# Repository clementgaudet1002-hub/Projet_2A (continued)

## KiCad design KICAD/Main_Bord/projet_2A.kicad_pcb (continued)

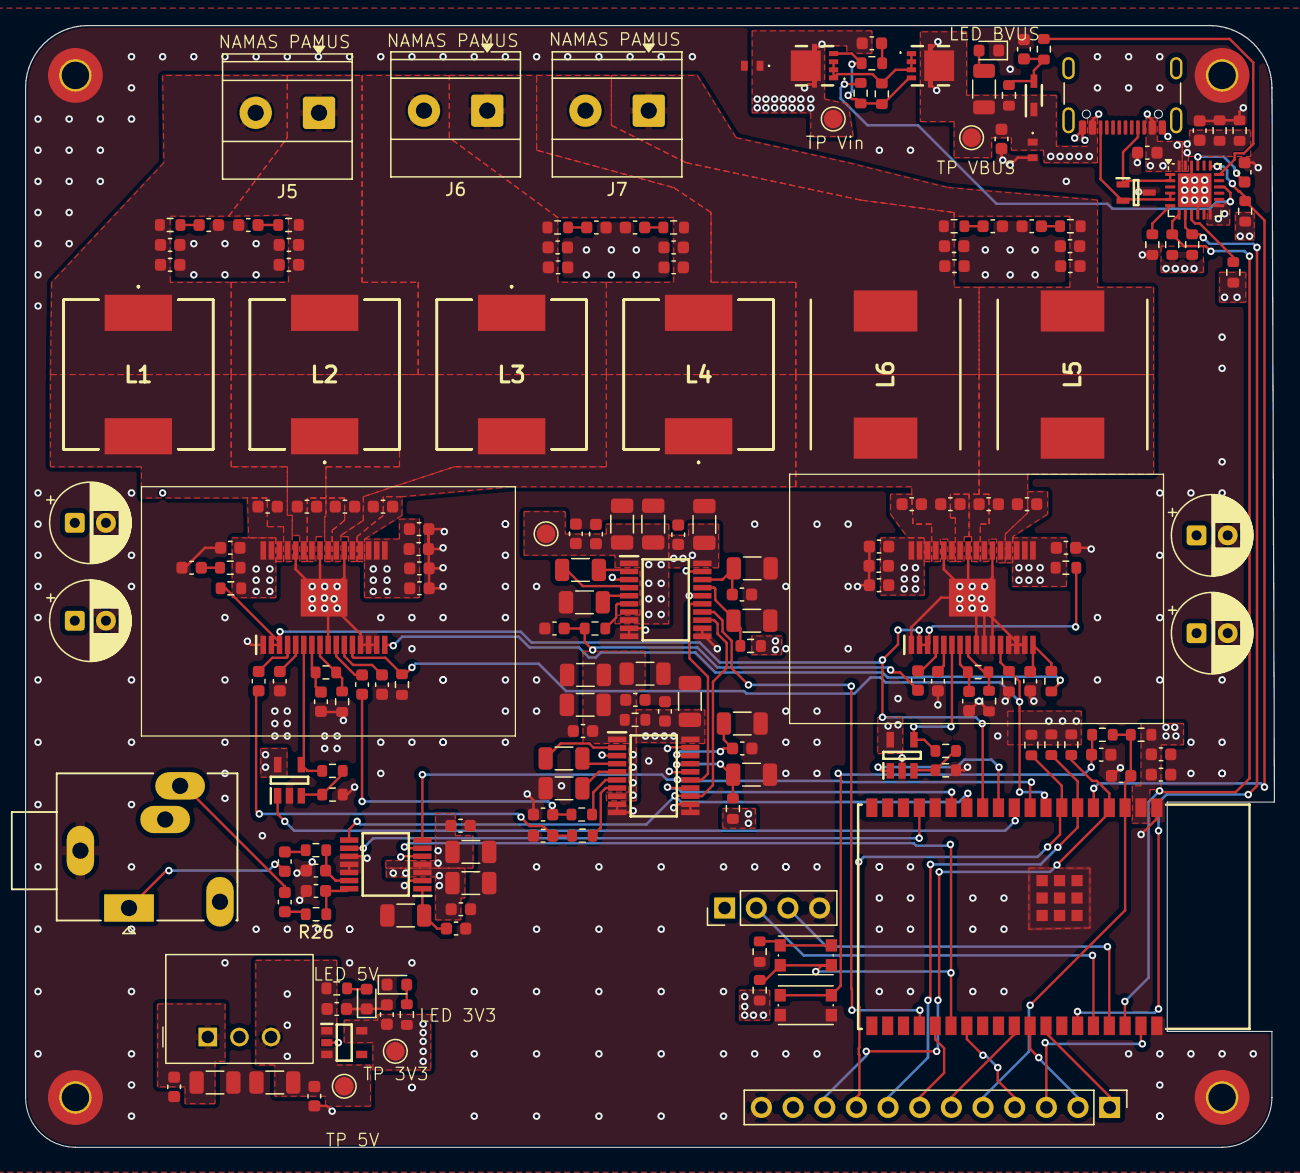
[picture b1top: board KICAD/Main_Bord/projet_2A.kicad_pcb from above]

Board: 4 copper layers, 100.2 x 90.0 mm, 195 parts (0 on the bottom side), 114 nets.

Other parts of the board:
L5, L6: 7447707100

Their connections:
unnamed 79: L5.1; also elsewhere on the board
unnamed 80: L6.2; also elsewhere on the board
unnamed 105: L5.2; also elsewhere on the board
unnamed 106: L6.1; also elsewhere on the board

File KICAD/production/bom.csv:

Designator,Footprint,Quantity,Value,LCSC Part #
"C1, C109, C16, C4, C51, C52, C54, C55, C57, C60, C64, C71, C73, C75, C78, C83, C85, C87, C89, C94, C95",0603,21,100n,
"C10, C15, C20, C22, C24, C25, C3, C39, C40, C41, C43, C44, C45, C6, C7, C9, C96",0603,17,1n,
"C100, C101, C102, C103, C108, C37, C38, C42, C8, C90, C93, C98, C99",0603,13,1u,
"C104, C105, C2, C26, C27, C28, C29, C91, C92",0603,9,10n,
C106,0603,1,4.7u,
C107,0603,1,22u,
"C11, C12, C13, C14, C46, C47, C48, C50",0603,8,220n,
"C110, C66, C67",0603,3,2.2n,
"C17, C5, C53, C56",CP_Radial_D6.3mm_P2.50mm,4,220u,
"C18, C19, C21, C23",0603,4,680n,
"C58, C59, C61, C65, C68, C69, C70, C76, C77, C82, C84, C86, C88, C97",1206,14,10u,
"C62, C63, C72, C74, C80, C81",1206,6,2.2u,
"D1, D3",ESDA25P351U1M,2,ESDA25P35-1U1M,
"D2, D6, D7",0603,3,LED,
D4,ESDA25W,1,ESDA25W,
D5,BAT54JFILM,1,BAT54JFILM,
"IC1, IC2",TPA3116D2QDADRQ1,2,TPA3116D2QDADRQ1,
"IC3, IC4",LM321SN3T1G,2,LM321SN3T1G,
IC5,ESP32WROVEREN16R8,1,ESP32-WROVER-E-N16R8,
"IC6, IC8",PCM5102AQPWRQ1,2,PCM5102AQPWRQ1,
IC7,PCM1808PW,1,PCM1808PW,
"J1, J9",PinHeader_1x12_P2.54mm_Vertical,2,Conn_01x12,
J10,PinHeader_1x04_P2.54mm_Vertical,1,Conn_01x04,
J2,USB_C_Receptacle_GCT_USB4105-xx-A_16P_TopMnt_Horizontal,1,USB_C_Receptacle_USB2.0_16P,
J3,PinHeader_1x09_P2.54mm_Vertical,1,Conn_01x09,
"J5, J6, J7","TerminalBlock_Phoenix_MKDS-1,5-2-5.08_1x02_P5.08mm_Horizontal",3,Conn_01x02,
J8,Jack_3.5mm_Ledino_KB3SPRS_Horizontal,1,AudioJack3_SwitchTR,
"L1, L2, L3, L4",7447706100,4,7447706100,
"L5, L6",7447707100,2,7447707100,
PS2,BU33SD5WG-TR,1,BU33SD5WG-TR,
"Q3, Q4",STL8N10F7,2,STL6P3LLH6,
"R1, R14, R15, R3, R33, R36, R37, R5",0603,8,100k,
R11,0603,1,47k,
R12,0603,1,75k,
"R13, R16, R2, R6, R7, R8, R9",0603,7,3.3,
"R18, R19, R22, R31, R52",0603,5,470,
R20,0603,1,2.2,
"R21, R23, R24, R25, R44, R45, R46, R51",0603,8,10k,
"R26, R27, R35",0603,3,100,
"R28, R42",0603,2,12k,
"R29, R30, R38, R39, R40",0603,5,1k,
"R32, R43",0603,2,13k,
R34,0603,1,22k,
R4,0603,1,20k,
R41,1206,1,4.7k,
"R47, R48, R49",0603,3,4.7k,
R50,0603,1,0,
SW1,RotaryEncoder_Alps_EC11E-Switch_Vertical_H20mm_CircularMountingHoles,1,RotaryEncoder_Switch,
SW2,SW_PUSH_6mm,1,SW_Push,
"SW3, SW4",SW_Push_1P1T_NO_CK_KMR2,2,SW_Push,
"TP2, TP4, TP6, TP7, TP8",TestPoint_Pad_D1.5mm,5,TestPoint,
U3,QFN-24-1EP_4x4mm_P0.5mm_EP2.7x2.7mm,1,STUSB4500QTR,
U6,U_Wurth_MagIC-FDSM_173010x42,1,173010542,

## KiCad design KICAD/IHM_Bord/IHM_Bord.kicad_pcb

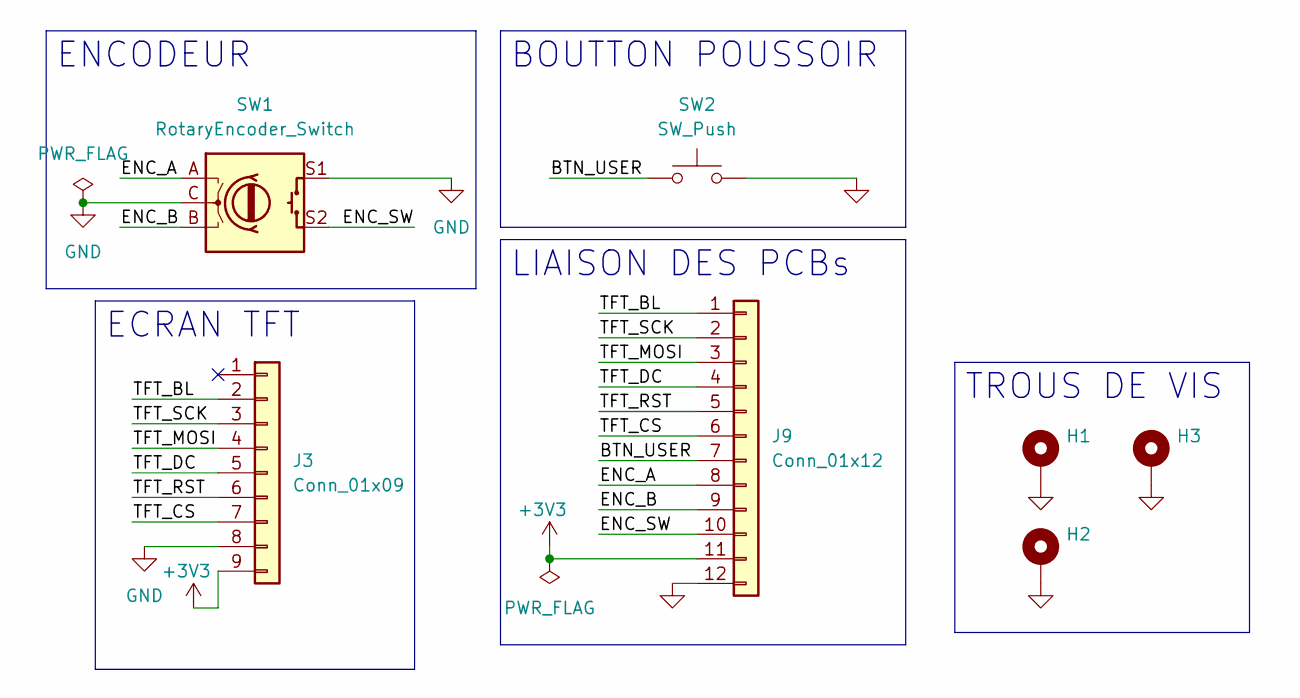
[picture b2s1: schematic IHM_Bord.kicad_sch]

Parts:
H1, H2, H3: MountingHole_Pad; MountingHole_2.2mm_M2_Pad_TopBottom
J3: Conn_01x09; PinHeader_1x09_P2.54mm_Vertical
J9: Conn_01x12; PinHeader_1x12_P2.54mm_Vertical
SW1: RotaryEncoder_Switch; RotaryEncoder_Alps_EC11E-Switch_Vertical_H20mm_CircularMoun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
SW2: SW_Push; SW_PUSH_6mm

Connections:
+3V3: J3.9, J9.11
/BTN_USER: J9.7, SW2.1
/ENC_A: J9.8, SW1.A
/ENC_B: J9.9, SW1.B
/ENC_SW: J9.10, SW1.S2
/TFT_BL: J3.2, J9.1
/TFT_CS: J3.7, J9.6
/TFT_DC: J3.5, J9.4
/TFT_MOSI: J3.4, J9.3
/TFT_RST: J3.6, J9.5
/TFT_SCK: J3.3, J9.2
GND: H1.1 (1_1), H2.1 (1_1), H3.1 (1_1), J3.8, J9.12, SW1.C, SW1.S1, SW2.2

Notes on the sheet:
ECRAN TFT
TROUS DE VIS
LIAISON DES PCBs
ENCODEUR
BOUTTON POUSSOIR

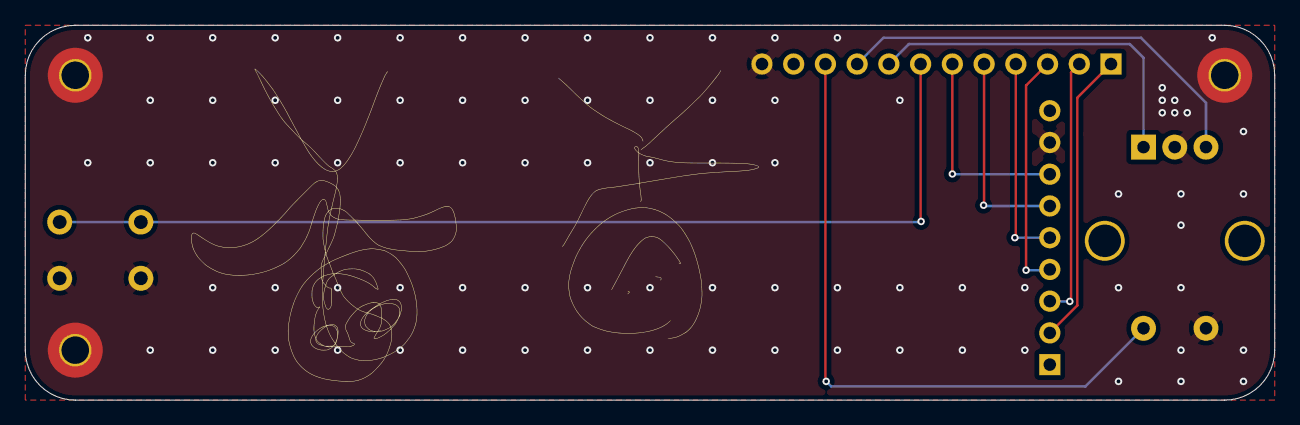
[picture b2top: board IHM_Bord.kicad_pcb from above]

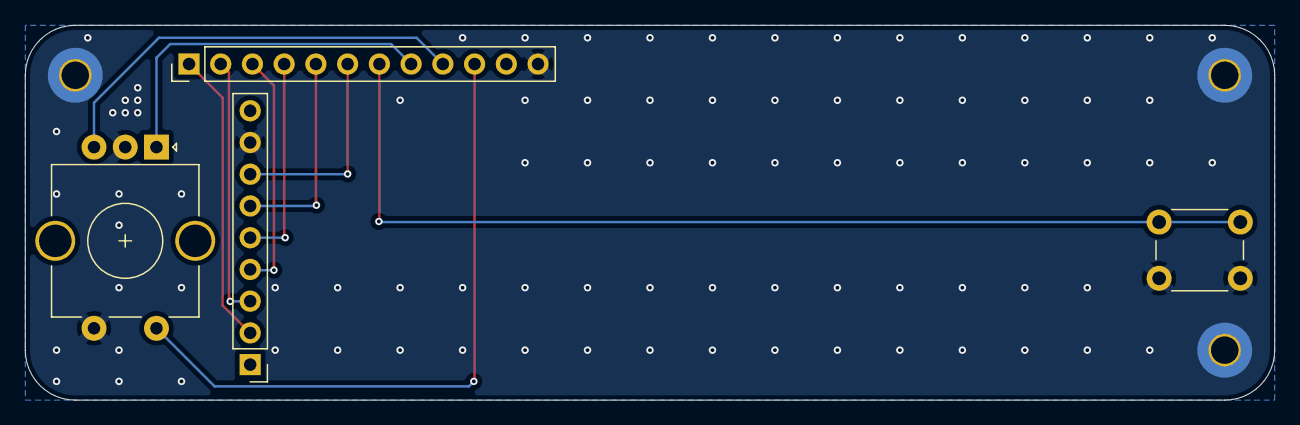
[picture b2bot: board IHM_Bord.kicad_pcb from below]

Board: 4 copper layers, 100.0 x 30.0 mm, 7 parts (4 on the bottom side), 12 nets.

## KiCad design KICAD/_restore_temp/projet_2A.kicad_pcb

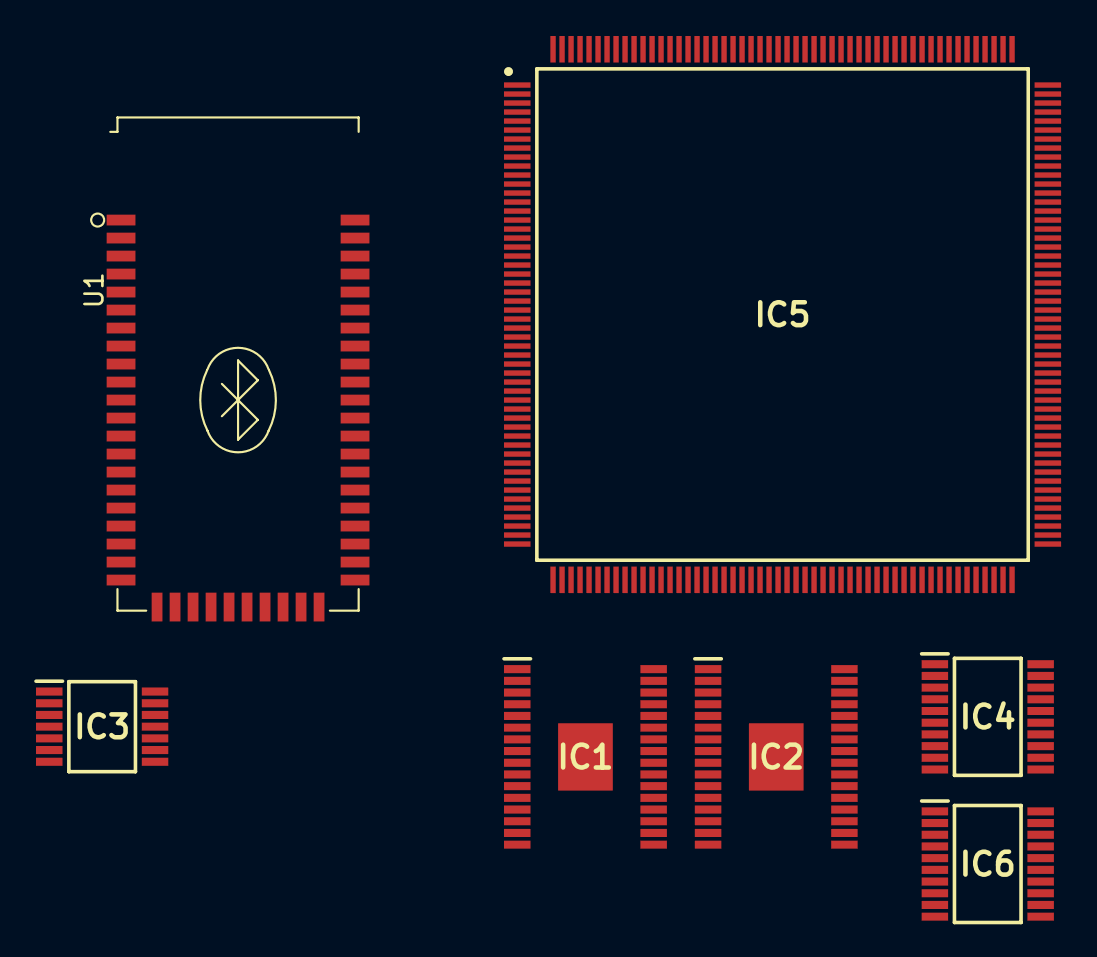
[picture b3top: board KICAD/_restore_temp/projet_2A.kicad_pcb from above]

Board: 2 copper layers, 7 parts (0 on the bottom side), 17 nets, no tracks yet.

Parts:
IC1, IC2: TPA3116D2QDADRQ1
IC3: PCM1808PW
IC4, IC6: PCM5102AQPWRQ1
IC5: STM32F746BGT6
U1: FSC-BT1026E; FSC-BT1026x

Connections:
+3.3V: IC3.4 (VDD), IC4.20 (DVDD), IC6.20 (DVDD), U1.33 (VBAT_IN), U1.34 (SYS_CTRL), U1.36 (VDD_IO)
+3.3VA: IC4.1 (CPVDD), IC4.8 (AVDD), IC6.1 (CPVDD), IC6.8 (AVDD)
/ADC_PCM1808/BCK/SAI1_SCK_A: IC3.8 (BCK), IC4.13 (BCK), IC5.4 (PE5), IC6.13 (BCK)
/ADC_PCM1808/DOUT/SAI1_SD_A: IC3.9 (DOUT), IC5.5 (PE6)
/ADC_PCM1808/LRCK/SAI1_FS_A: IC3.7 (LRCK), IC4.15 (LRCK), IC5.3 (PE4), IC6.15 (LRCK)
/ADC_PCM1808/SCKI/SAI1_MCLK_A: IC3.6 (SCKI), IC5.1 (PE2)
/Bluetooth/USART_RX: IC5.143 (PA9), U1.14 (BT_RX/PI04)
/Bluetooth/USART_TX: IC5.144 (PA10), U1.13 (BT_TX/PI05)
/DAC_PCM5102A/DIN/SAI1_SD_A: IC4.14 (DIN), IC5.2 (PE3), IC6.14 (DIN)
/STM/AMP_MUTE: IC1.12 (MUTE), IC2.12 (MUTE), IC5.54 (PA5)
/STM/AMP_SD: IC1.2 (SD), IC1.3 (FAULT), IC2.2 (SD), IC2.3 (FAULT), IC5.53 (PA4)
GND: IC1.1 (MODSEL), IC1.9 (GND_1), IC1.13 (AM2), IC1.14 (AM1), IC1.15 (AM0), IC1.22 (GND_2), IC1.25 (GND_3), IC1.28 (GND_4), IC1.33 (GND_5), IC2.1 (MODSEL), IC2.9 (GND_1), IC2.10 (LINP), IC2.11 (LINN), IC2.13 (AM2), IC2.14 (AM1), IC2.15 (AM0), IC2.22 (GND_2), IC2.25 (GND_3), IC2.28 (GND_4), IC2.33 (GND_5), IC3.2 (AGND), IC3.5 (DGND), IC3.10 (MD0), IC3.11 (MD1), IC3.12 (FMT), IC4.3 (CPGND), IC4.9 (AGND), IC4.10 (DEMP), IC4.11 (FLT), IC4.12 (SCK), IC4.16 (FMT), IC4.19 (DGND), IC6.3 (CPGND), IC6.9 (AGND), IC6.10 (DEMP), IC6.11 (FLT), IC6.16 (FMT), IC6.19 (DGND), U1.1 (GND), U1.22 (GND), U1.32 (GND), U1.46 (AUDIO_HPR_N), U1.48 (AUDIO_HPL_N), U1.50 (GND), U1.52 (GND)
unnamed: IC1.6 (PLIMIT), IC1.7 (GVDD)
unnamed: IC2.6 (PLIMIT), IC2.7 (GVDD)
unnamed: IC2.21 (OUTNL), IC2.23 (OUTPL)
unnamed: IC2.27 (OUTNR), IC2.29 (OUTPR)
PVCC: IC1.17 (AVCC), IC1.18 (PVCC_1), IC1.19 (PVCC_2), IC1.31 (PVCC_3), IC1.32 (PVCC_4), IC2.17 (AVCC), IC2.18 (PVCC_1), IC2.19 (PVCC_2), IC2.31 (PVCC_3), IC2.32 (PVCC_4)

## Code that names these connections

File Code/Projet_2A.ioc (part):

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Mcu.Name=STM32F446R(C-E)Tx
Mcu.Package=LQFP64
Mcu.UserName=STM32F446RETx
PA0-WKUP.GPIOParameters=GPIO_Label
PA0-WKUP.GPIO_Label=ENC_A
PA0-WKUP.Signal=S_TIM2_CH1_ETR
PA1.GPIOParameters=GPIO_Label
PA1.GPIO_Label=ENC_B
PA1.Signal=S_TIM2_CH2
PA10.GPIOParameters=GPIO_Label
PA10.GPIO_Label=BT_TX
PA10.Mode=Asynchronous
PA10.Signal=USART1_RX
PA13.GPIOParameters=GPIO_Label
PA13.GPIO_Label=SWDIO
PA13.Signal=SYS_JTMS-SWDIO
PA14.GPIOParameters=GPIO_Label
PA14.GPIO_Label=SWCLK
PA14.Signal=SYS_JTCK-SWCLK
PA15.GPIOParameters=GPIO_Label
PA15.GPIO_Label=I2S_WS
PA15.Signal=I2S3_WS
PA2.GPIOParameters=GPIO_Label
PA2.GPIO_Label=ENC_SW
PA2.Signal=GPXTI2
PA3.GPIOParameters=GPIO_Label
PA3.GPIO_Label=BTN_USER
PA3.Signal=GPXTI3
PA4.GPIOParameters=GPIO_Label
PA4.GPIO_Label=AMP_PLIMIT
PA4.Signal=COMP_DAC1_group
PA5.GPIOParameters=GPIO_Label
PA5.GPIO_Label=AMP_SUB_PLIMIT
PA5.Signal=COMP_DAC2_group
PA7.GPIOParameters=GPIO_Label
PA7.GPIO_Label=I2S_DIN2
PA7.Signal=I2S1_SD
PA8.GPIOParameters=GPIO_Label
PA8.GPIO_Label=USB_SCL
PA8.Mode=I2C
PA8.Signal=I2C3_SCL
PA9.GPIOParameters=GPIO_Label
PA9.GPIO_Label=BT_RX
PA9.Mode=Asynchronous
PA9.Signal=USART1_TX
PB0.GPIOParameters=GPIO_Label
PB0.GPIO_Label=AMP_SD
PB0.Signal=GPIO_Output
PB1.GPIOParameters=GPIO_Label
PB1.GPIO_Label=AMP_MUTE
PB1.Signal=GPIO_Output
PB10.GPIOParameters=GPIO_Label
PB10.GPIO_Label=AMP_SUB_MUTE
PB10.Signal=GPIO_Output
PB12.GPIOParameters=GPIO_Label
PB12.GPIO_Label=I2S_LRCK
PB12.Signal=I2S2_WS
PB13.GPIOParameters=GPIO_Label
PB13.GPIO_Label=I2S_BCK
PB13.Signal=I2S2_CK
PB15.GPIOParameters=GPIO_Label
PB15.GPIO_Label=I2S_DIN1
PB15.Signal=I2S2_SD
PB2.GPIOParameters=GPIO_Label
PB2.GPIO_Label=AMP_SUB_SD
PB2.Signal=GPIO_Output
PB3.GPIOParameters=GPIO_Label
PB3.GPIO_Label=TFT_SCK
PB3.Signal=I2S1_CK
PB4.GPIOParameters=GPIO_Label
PB4.GPIO_Label=TFT_CS
PB4.Signal=GPIO_Output
PB5.GPIOParameters=GPIO_Label
PB5.GPIO_Label=TFT_MOSI
PB5.Signal=SPI1_MOSI
PB6.GPIOParameters=GPIO_Label
PB6.GPIO_Label=TFT_DC
PB6.Signal=GPIO_Output
PB7.GPIOParameters=GPIO_Label
PB7.GPIO_Label=TFT_RST
PB7.Signal=GPIO_Output
PB8.GPIOParameters=GPIO_Label
PB8.GPIO_Label=TFT_BL
PB8.Signal=S_TIM4_CH3
PC0.GPIOParameters=GPIO_Label
PC0.GPIO_Label=JACK_DET
PC0.Signal=GPXTI0
PC1.GPIOParameters=GPIO_Label
PC1.GPIO_Label=AMP_SUB_SD
PC1.Signal=GPIO_Output
PC10.GPIOParameters=GPIO_Label
PC10.GPIO_Label=I2S_CK
PC10.Signal=I2S3_CK
PC12.GPIOParameters=GPIO_Label
PC12.GPIO_Label=I2S_DOUT
PC12.Signal=I2S3_SD
PC2.GPIOParameters=GPIO_Label
PC2.GPIO_Label=AMP_SUB_MUTE
PC2.Signal=GPIO_Output
PC6.GPIOParameters=GPIO_Label
PC6.GPIO_Label=I2S_SCKI
PC6.Signal=I2S2_MCK
PC8.GPIOParameters=GPIO_Label
PC8.GPIO_Label=USB_ALERT
PC8.Signal=GPXTI8
PC9.GPIOParameters=GPIO_Label
PC9.GPIO_Label=USB_SDA
PC9.Mode=I2C
PC9.Signal=I2C3_SDA
board=custom
